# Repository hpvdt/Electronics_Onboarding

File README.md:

# Electronics_Onboarding
A set of onboarding exercises for new members to familiarize themselves with the basics of hardware and firmware design

## Hardware Design
A key component of the HPVDT electronics team's work is Hardware design. Printed circuit boards(PCBs) are used to create embedded systems that fetch, interpret, and display important sensor information to the rider or the land crew. To create these PCBs, our team currently uses [Kicad](Kicad.com), a free and open-source software available on Linux, Windows and MacOS.

To learn about hardware design you can begin by clicking on the folder "Hardware Design".

## Firmware Design

Once our hardware has been designed and fabricated, many of our systems use microcontroller chips that interpret readings from sensors on board. To learn about firmware design you can click on the folder "Firmware Design".

### In progress

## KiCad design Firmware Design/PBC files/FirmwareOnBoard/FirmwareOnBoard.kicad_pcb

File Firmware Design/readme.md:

# Firmware OnBoard
### Aryan Ghosh

The OnBoard is an embedded system with several common perhipheral devices that you will see in HPVDT vehicles. Speed sensors, LED displays, and USB-C communication are just a few of the peripherals on this board.

This board serves as a sandbox for you to practice and improve your firmware development skills.

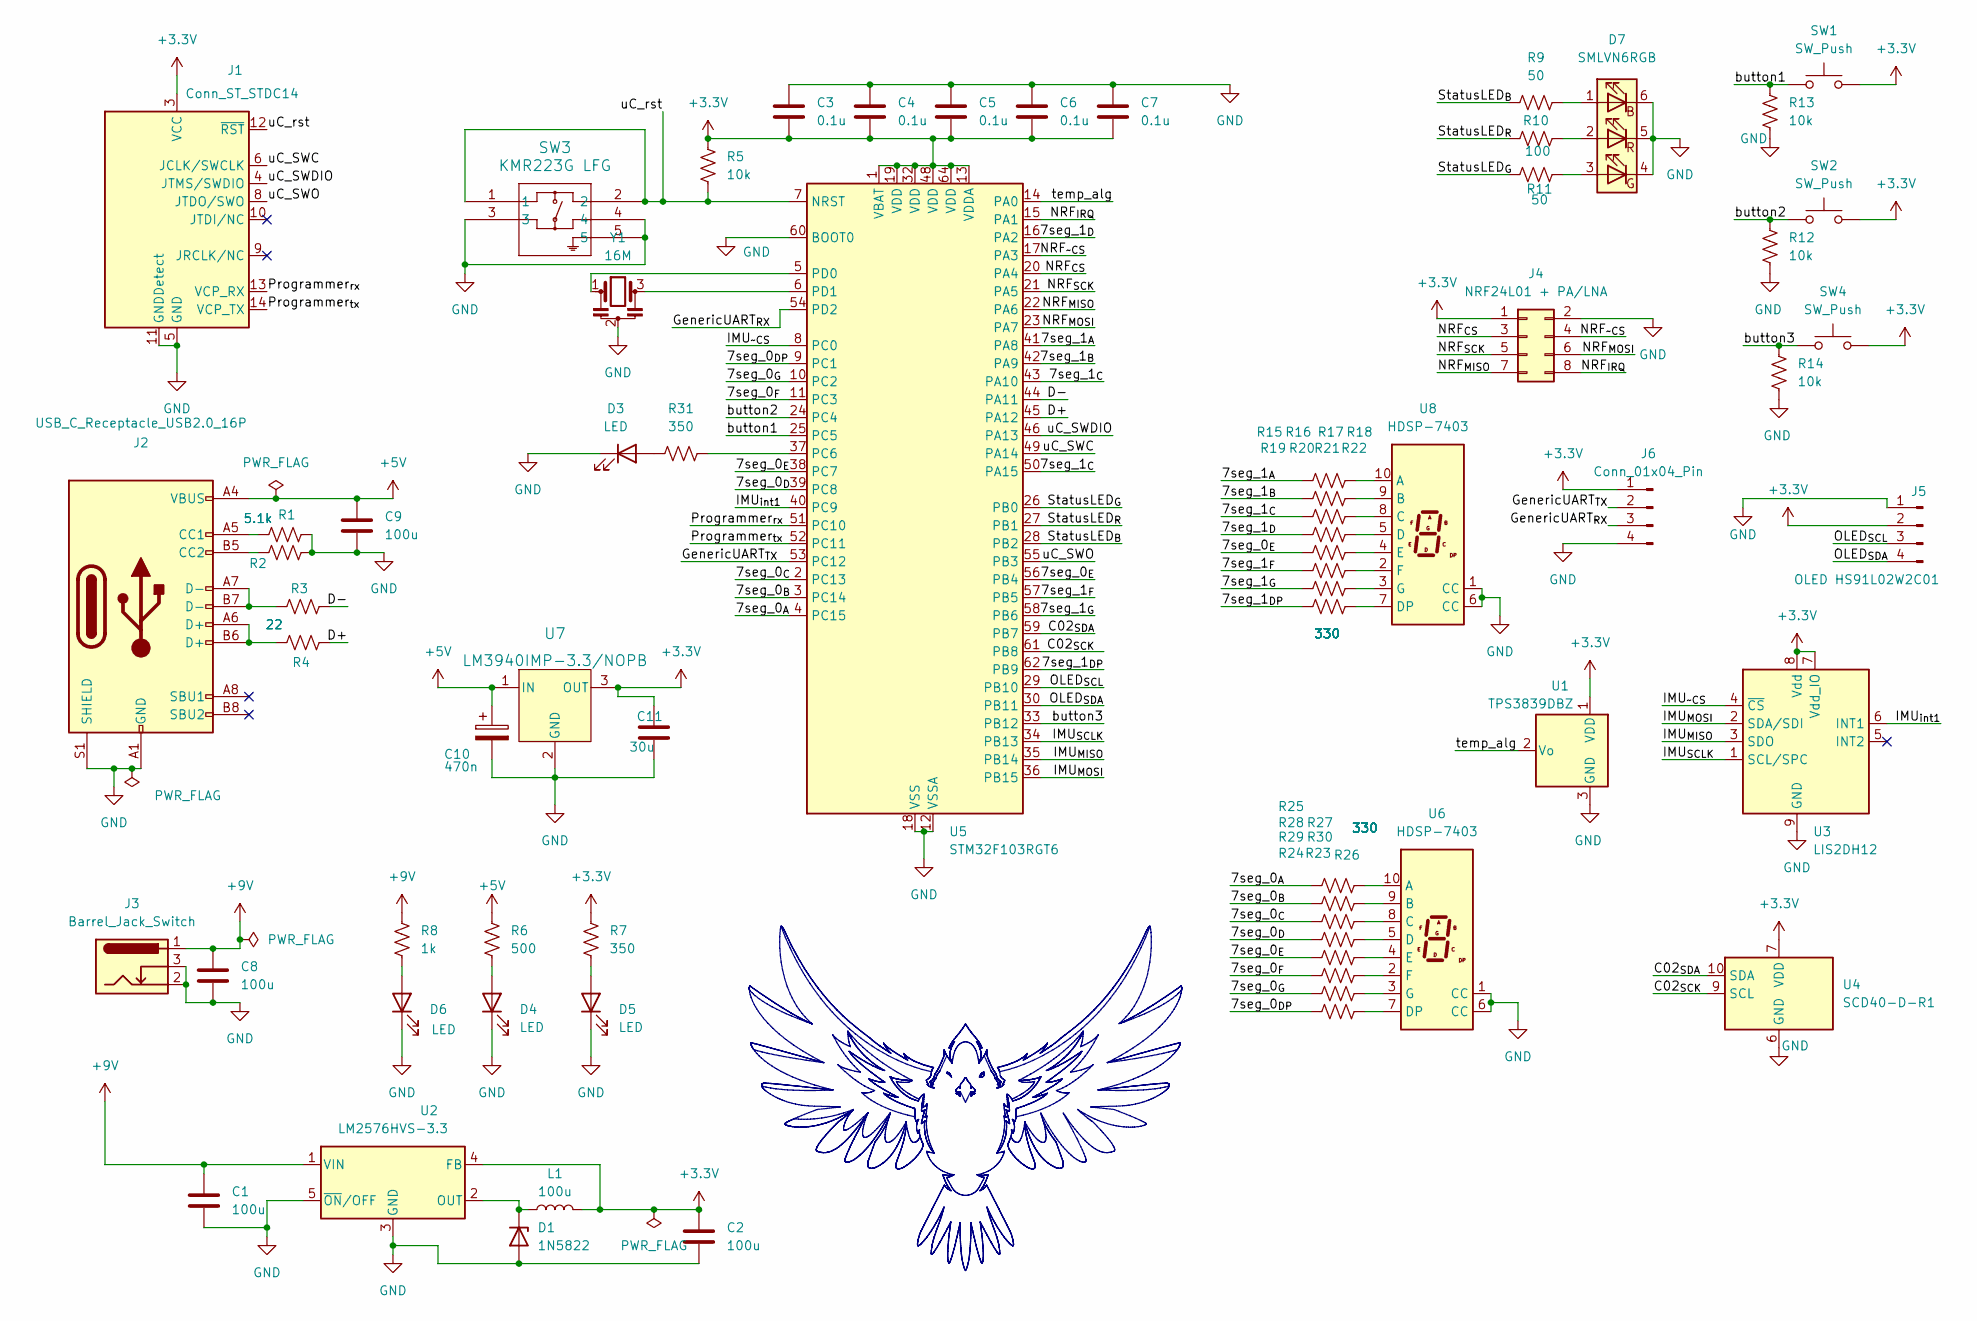
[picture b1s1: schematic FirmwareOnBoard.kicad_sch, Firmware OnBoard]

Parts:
C1, C2, C8, C9: 100u; C_0603_1608Metric
C3, C4, C5, C6, C7: 0.1u; C_0603_1608Metric
C10: 470n; C_0603_1608Metric; LCSC C106250
C11: 30u; C_0603_1608Metric; LCSC C90806
D1: 1N5822; D_DO-15_P12.70mm_Horizontal
D3: LED; LED_0805_2012Metric
D4, D5, D6: LED; LED_0805_2012Metric; LCSC C965818
D7: SMLVN6RGB; LED_ROHM_SMLVN6; LCSC C2842809
J1: Conn_ST_STDC14; PinHeader_2x07_P1.27mm_Vertical_SMD
J2: USB_C_Receptacle_USB2.0_16P; USB_C_Receptacle_HRO_TYPE-C-31-M-12
J3: Barrel_Jack_Switch; BarrelJack_Kycon_KLDX-0202-xC_Horizontal
J4: NRF24L01 + PA/LNA; PinHeader_2x04_P2.54mm_Vertical
J5: OLED HS91L02W2C01; PinHeader_1x04_P2.54mm_Vertical
J6: Conn_01x04_Pin; TerminalBlock_Altech_AK300-4_P5.00mm
L1: 100u; L_0201_0603Metric
R1, R2: 5.1k; R_0201_0603Metric
R3, R4: 22; R_0201_0603Metric
R5, R12, R13, R14: 10k; R_0603_1608Metric
R6: 500; R_0603_1608Metric; LCSC C23025
R7, R31: 350; R_0603_1608Metric; LCSC C23025
R8: 1k; R_0603_1608Metric; LCSC C23025
R9, R11: 50; R_0603_1608Metric; LCSC C849792
R10: 100; R_0603_1608Metric; LCSC C105588
R15, R16, R17, R18, R19, R20, R21, R22, R23, R24, R25, R26, R27, R28, R29, R30: 330; R_0603_1608Metric
SW1, SW2, SW4: SW_Push; SW_Cherry_MX1A_1.00u_PCB
SW3: KMR223G LFG; KMR2_G_CNK; LCSC C221678
U1: TPS3839DBZ; SOT-23
U2: LM2576HVS-3.3; TO-263-5_TabPin3
U3: LIS2DH12; LGA-14_2x2mm_P0.35mm_LayoutBorder3x4y
U4: SCD40-D-R1; Sensirion_SCD4x-1EP_10.1x10.1mm_P1.25mm_EP4.8x4.8mm
U5: STM32F103RGT6; LQFP-64_10x10mm_P0.5mm
U6, U8: HDSP-7403; HDSP-7401NEWADJUSETED
U7: LM3940IMP-3.3/NOPB; MP04A; LCSC C140319
Y1: 16M; Resonator_SMD_Murata_CSTxExxV-3Pin_3.0x1.1mm; LCSC C341522

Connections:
+3.3V: C2.1, C3.1, C4.1, C5.1, C6.1, C7.1, C11.1, J1.3 (VCC), J4.1, J5.2, J6.1, L1.2, R5.1, R7.1, SW1.2, SW2.2, SW4.2, U1.1 (VDD), U2.4 (FB), U3.7 (Vdd_IO), U3.8 (Vdd), U4.7 (VDD), U4.19 (VDD), U5.1 (VBAT), U5.13 (VDDA), U5.19 (VDD), U5.32 (VDD), U5.48 (VDD), U5.64 (VDD), U7.3 (OUT)
+5V: C9.1, C10.1, J2.A4 (VBUS), J2.A9 (VBUS), J2.B4 (VBUS), J2.B9 (VBUS), R6.1, U7.1 (IN)
+9V: C1.1, C8.1, J3.1, R8.1, U2.1 (VIN)
/7seg_0_{A}: R23.1, U5.4 (PC15)
/7seg_0_{B}: R24.1, U5.3 (PC14)
/7seg_0_{C}: R25.1, U5.2 (PC13)
/7seg_0_{DP}: R30.1, U5.9 (PC1)
/7seg_0_{D}: R26.1, U5.39 (PC8)
/7seg_0_{E}: R19.1, R27.1, U5.38 (PC7), U5.56 (PB4)
/7seg_0_{F}: R28.1, U5.11 (PC3)
/7seg_0_{G}: R29.1, U5.10 (PC2)
/7seg_1_{A}: R15.1, U5.41 (PA8)
/7seg_1_{B}: R16.1, U5.42 (PA9)
/7seg_1_{C}: R17.1, U5.43 (PA10), U5.50 (PA15)
/7seg_1_{DP}: R22.1, U5.62 (PB9)
/7seg_1_{D}: R18.1, U5.16 (PA2)
/7seg_1_{F}: R20.1, U5.57 (PB5)
/7seg_1_{G}: R21.1, U5.58 (PB6)
/C02_{SCK}: U4.9 (SCL), U5.61 (PB8)
/C02_{SDA}: U4.10 (SDA), U5.59 (PB7)
/D+: R4.1, U5.45 (PA12)
/D-: R3.1, U5.44 (PA11)
/GenericUART_{RX}: J6.3, U5.54 (PD2)
/GenericUART_{TX}: J6.2, U5.53 (PC12)
/IMU_{MISO}: U3.3 (SDO), U5.35 (PB14)
/IMU_{MOSI}: U3.2 (SDA/SDI), U5.36 (PB15)
/IMU_{SCLK}: U3.1 (SCL/SPC), U5.34 (PB13)
/IMU_{int1}: U3.6 (INT1), U5.40 (PC9)
/IMU_{~CS}: U3.4 (~CS), U5.8 (PC0)
/NRF_{CS}: J4.3, U5.20 (PA4)
/NRF_{IRQ}: J4.8, U5.15 (PA1)
/NRF_{MISO}: J4.7, U5.22 (PA6)
/NRF_{MOSI}: J4.6, U5.23 (PA7)
/NRF_{SCK}: J4.5, U5.21 (PA5)
/NRF_{~CS}: J4.4, U5.17 (PA3)
/OLED_{SCL}: J5.3, U5.29 (PB10)
/OLED_{SDA}: J5.4, U5.30 (PB11)
/Programmer_{rx}: J1.13 (VCP_RX), U5.51 (PC10)
/Programmer_{tx}: J1.14 (VCP_TX), U5.52 (PC11)
/StatusLED_{B}: R9.1, U5.28 (PB2)
/StatusLED_{G}: R11.1, U5.26 (PB0)
/StatusLED_{R}: R10.1, U5.27 (PB1)
/button1: R13.1, SW1.1, U5.25 (PC5)
/button2: R12.1, SW2.1, U5.24 (PC4)
/button3: R14.1, SW4.1, U5.33 (PB12)
/temp_alg: U1.2 (Vo), U5.14 (PA0)
/uC_SWC: J1.6 (JCLK/SWCLK), U5.49 (PA14)
/uC_SWDIO: J1.4 (JTMS/SWDIO), U5.46 (PA13)
/uC_SWO: J1.8 (JTDO/SWO), U5.55 (PB3)
/uC_rst: J1.12 (~RST), R5.2, SW3.1, SW3.2, U5.7 (NRST)
GND: C1.2, C2.2, C3.2, C4.2, C5.2, C6.2, C7.2, C8.2, C9.2, C10.2, C11.2, D1.2 (A), D3.1 (K), D4.1 (K), D5.1 (K), D6.1 (K), D7.4 (GK), D7.5 (RK), D7.6 (BK), J1.5 (GND), J1.7 (GND), J1.11 (GNDDetect), J2.A1 (GND), J2.A12 (GND), J2.B1 (GND), J2.B12 (GND), J2.S1 (SHIELD), J3.2, J3.3, J4.2, J5.1, J6.4, R1.1, R2.1, R12.2, R13.2, R14.2, SW3.3, SW3.4, SW3.5, U1.3 (GND), U2.3 (GND), U2.5 (~ON/OFF), U3.9 (GND), U3.10 (GND), U3.11 (GND), U3.12 (GND), U3.13 (GND), U3.14 (GND), U4.6 (GND), U4.20 (GND), U4.21 (GND), U5.12 (VSSA), U5.18 (VSS), U5.31 (VSS), U5.47 (VSS), U5.60 (BOOT0), U5.63 (VSS), U6.1 (CC), U6.6 (CC), U7.2 (GND), U7.4 (GND), U8.1 (CC), U8.6 (CC), Y1.2
unnamed: D1.1 (K), L1.1, U2.2 (OUT)
unnamed: D3.2 (A), R31.2
unnamed: D4.2 (A), R6.2
unnamed: D5.2 (A), R7.2
unnamed: D6.2 (A), R8.2
unnamed: D7.1 (BA), R9.2
unnamed: D7.3 (GA), R11.2
unnamed: D7.2 (RA), R10.2
unnamed: J2.A5 (CC1), R1.2
unnamed: J2.B5 (CC2), R2.2
unnamed: J2.A6 (D+), J2.B6 (D+), R4.2
unnamed: J2.A7 (D-), J2.B7 (D-), R3.2
unnamed: R31.1, U5.37 (PC6)
unnamed: U5.5 (PD0), Y1.1
unnamed: U5.6 (PD1), Y1.3
unnamed: R23.2, U6.10 (A)
unnamed: R24.2, U6.9 (B)
unnamed: R25.2, U6.8 (C)
unnamed: R26.2, U6.5 (D)
unnamed: R30.2, U6.7 (DP)
unnamed: R27.2, U6.4 (E)
unnamed: R28.2, U6.2 (F)
unnamed: R29.2, U6.3 (G)
unnamed: R15.2, U8.10 (A)
unnamed: R16.2, U8.9 (B)
unnamed: R17.2, U8.8 (C)
unnamed: R18.2, U8.5 (D)
unnamed: R22.2, U8.7 (DP)
unnamed: R19.2, U8.4 (E)
unnamed: R20.2, U8.2 (F)
unnamed: R21.2, U8.3 (G)

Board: 4 copper layers, 68 parts (0 on the bottom side), 82 nets, no tracks yet.

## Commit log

2024-09-20 Create readme.md for hardware design
2024-09-20 Create readme.md for firmware
2024-11-03 Began 1st scghematic draft
2024-11-03 Sourced MCU
2024-11-04 Added New MCU and many peripherals
2024-11-08 Completed 1st draft of schematic
    Filled ALL MCU pin allocations lol
    2 seven seg displays (if hex, can represent 0-256)
2024-11-08 Added Files from Flightstick
2024-11-09 Complete first draft of layout placement
2024-11-15 Removed backups
2024-11-15 Added comments
